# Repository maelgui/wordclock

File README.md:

# Wordclock

## Building the clock

This repository contains every files needed to build the clock

- PCB
- Vinyle cutout layout
- 3D model for diffuser

## Using the clock

Firmware for the clock and android app for managing it can be found here :

- https://github.com/maelgui/wordclock-firmware
- https://github.com/maelgui/wordclock-manager

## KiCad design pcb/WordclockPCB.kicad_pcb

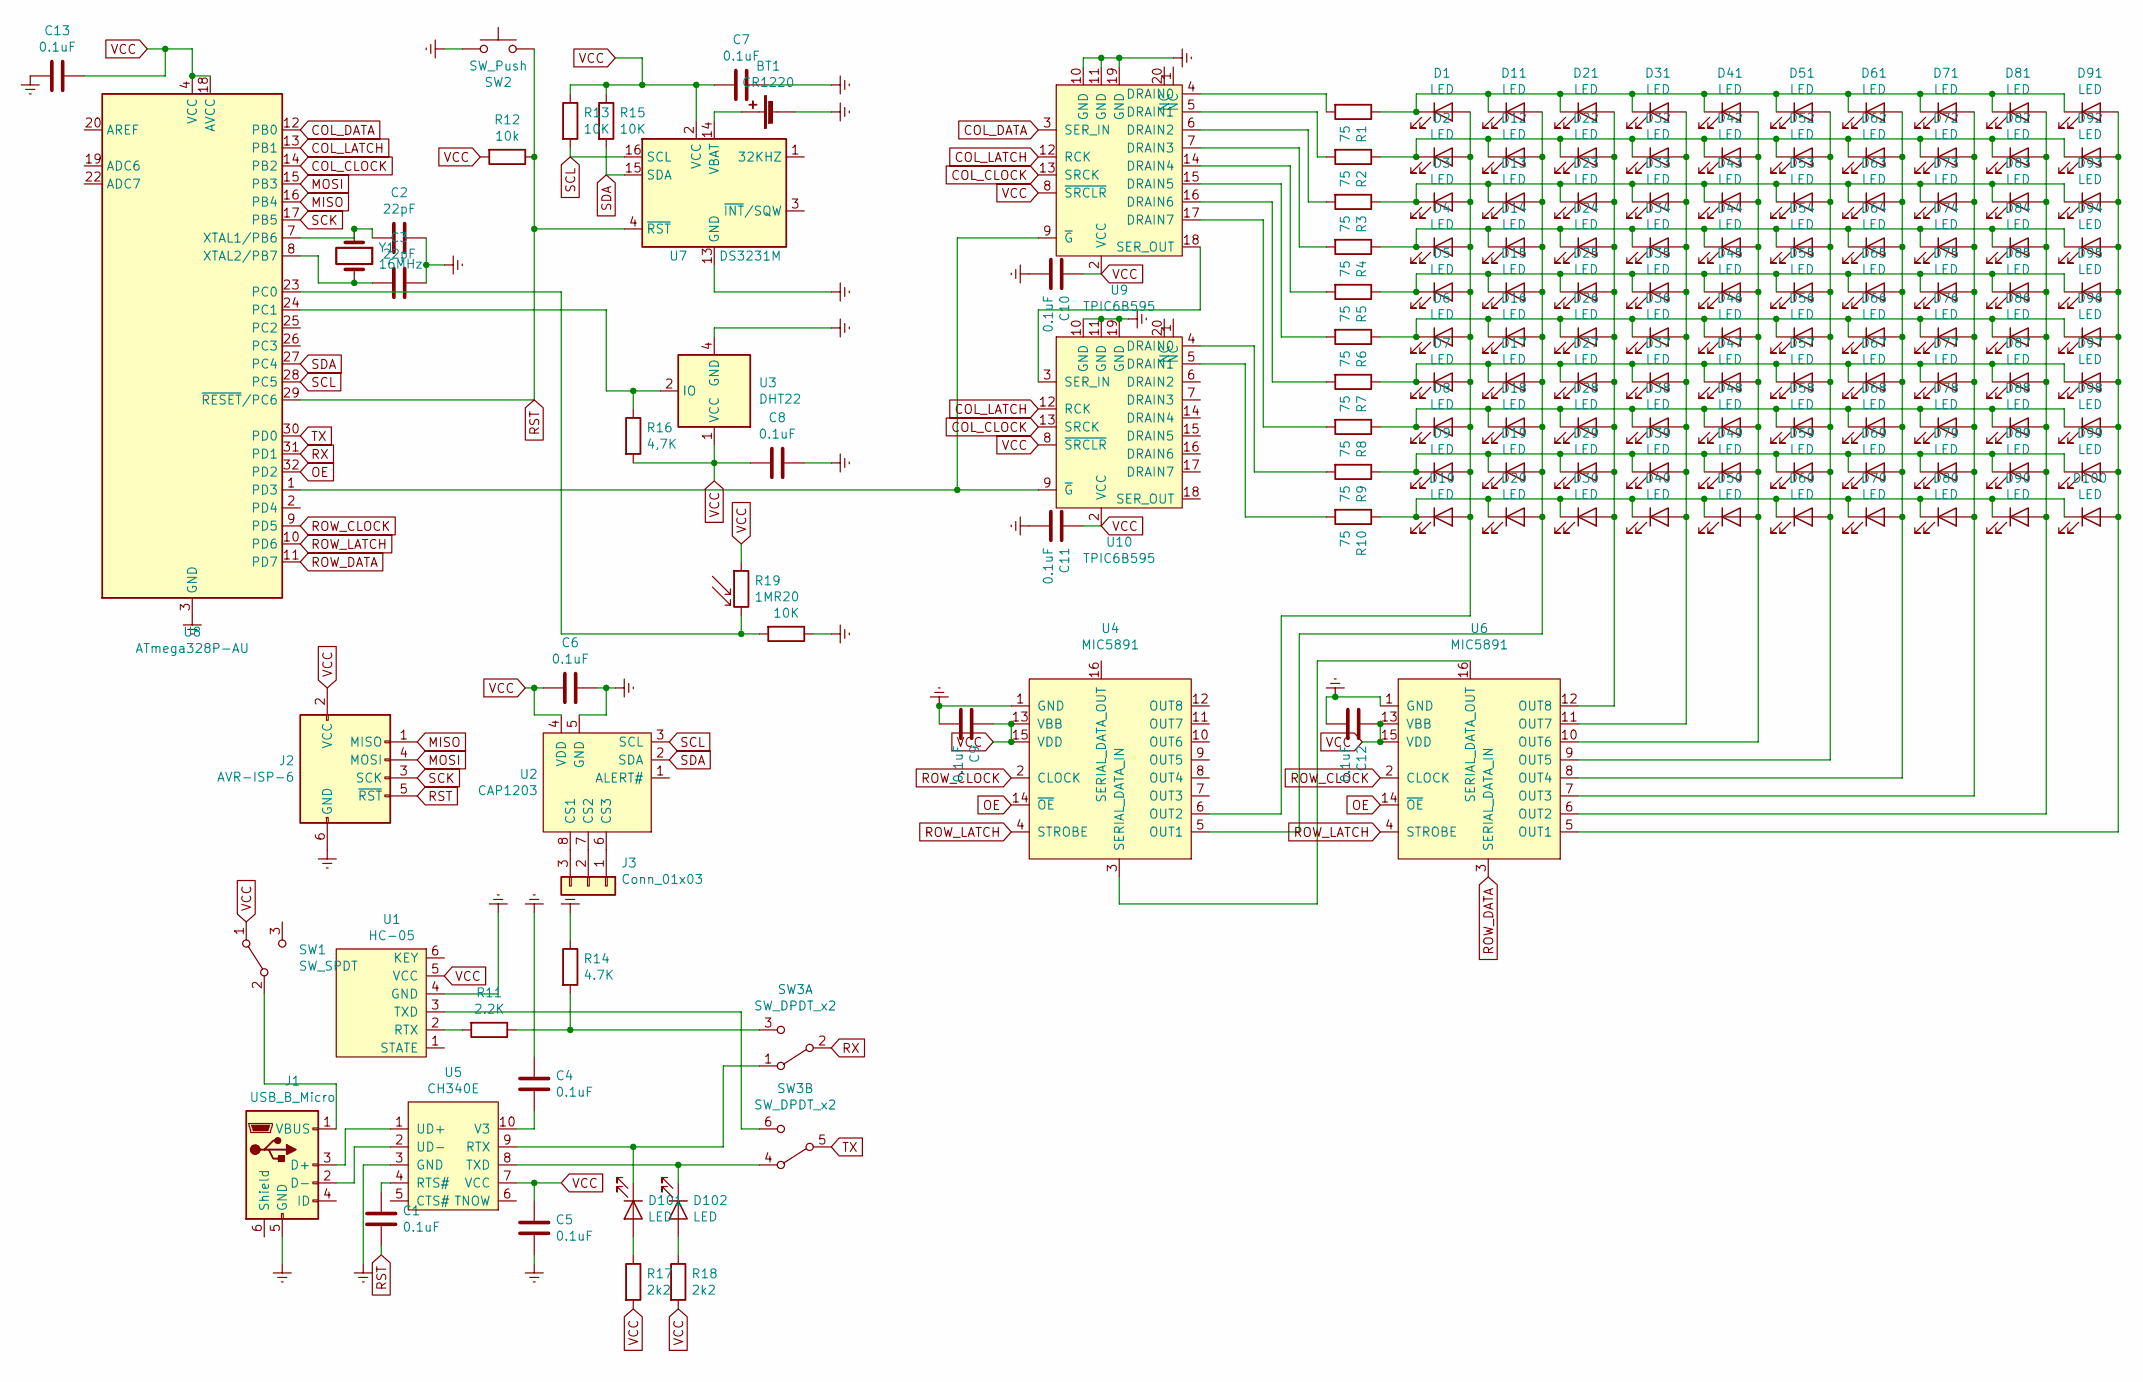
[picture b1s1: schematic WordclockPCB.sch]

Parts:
BT1: CR1220; BatteryHolder_MPD_BC2003_1x2032
C1, C4, C5, C6, C7, C8, C9, C10, C11, C12, C13: 0.1uF; C_0805_2012Metric
C2, C3: 22pF; C_0805_2012Metric
D1, D2, D3, D4, D5, D6, D7, D8, D9, D10, D11, D12, D13, D14, D15, D16, D17, D18, D19, D20, D21, D22, D23, D24, D25, D26, D27, D28, D29, D30, D31, D32, D33, D34, D35, D36, D37, D38, D39, D40, D41, D42, D43, D44, D45, D46, D47, D48, D49, D50, D51, D52, D53, D54, D55, D56, D57, D58, D59, D60, D61, D62, D63, D64, D65, D66, D67, D68, D69, D70, D71, D72, D73, D74, D75, D76, D77, D78, D79, D80, D81, D82, D83, D84, D85, D86, D87, D88, D89, D90, D91, D92, D93, D94, D95, D96, D97, D98, D99, D100: LED; LED_1210_3225Metric_Pad1.42x2.65mm_HandSolder
D101, D102: LED; LED_0805_2012Metric
J1: USB_B_Micro; USB_Micro-B_Amphenol_10103594-0001LF_Horizontal
J2: AVR-ISP-6; PinHeader_2x03_P2.54mm_Vertical_SMD
J3: Conn_01x03; PinHeader_1x03_P2.54mm_Vertical
R1, R2, R3, R4, R5, R6, R7, R8, R9, R10: 75; R_0805_2012Metric
R11: 2.2K; R_0805_2012Metric
R12: 10k; R_0805_2012Metric
R13, R15, R20: 10K; R_0805_2012Metric
R14: 4.7K; R_0805_2012Metric
R16: 4,7K; R_0805_2012Metric
R17, R18: 2k2; R_0805_2012Metric
R19: 1M; R_LDR_4.9x4.2mm_P2.54mm_Vertical
SW1: SW_SPDT; SW_SPDT_CK-JS102011SAQN
SW2: SW_Push; SW_Push_1P1T_NO_6x6mm_H9.5mm
SW3: SW_DPDT_x2; SW_JS202011SCQN
U1: HC-05; PinHeader_1x06_P2.54mm_Vertical
U2: CAP1203; SOIC-8_3.9x4.9mm_P1.27mm
U3: DHT22; Aosong_DHT11_5.5x12.0_P2.54mm
U4, U6: MIC5891; SOIC-16W_7.5x10.3mm_P1.27mm
U5: CH340E; TSSOP-10_3x3mm_P0.5mm
U7: DS3231M; SOIC-16W_7.5x10.3mm_P1.27mm
U8: ATmega328P-AU; TQFP-32_7x7mm_P0.8mm
U9, U10: TPIC6B595; SOIC-20W_7.5x12.8mm_P1.27mm
Y1: 16MHz; Crystal_SMD_HC49-SD_HandSoldering

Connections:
COL_CLOCK: U8.14 (PB2), U9.13 (SRCK), U10.13 (SRCK)
COL_DATA: U8.12 (PB0), U9.3 (SER_IN)
COL_LATCH: U8.13 (PB1), U9.12 (RCK), U10.12 (RCK)
Earth: BT1.2 (-), C2.1, C3.1, C4.2, C5.1, C6.1, C7.2, C8.2, C9.1, C10.1, C11.1, C12.1, C13.2, J1.5 (GND), J2.6 (GND), R14.1, R20.1, SW2.1, U1.4 (GND), U2.5 (GND), U3.4 (GND), U4.1 (GND), U5.3 (GND), U6.1 (GND), U7.5 (GND), U7.6 (GND), U7.7 (GND), U7.8 (GND), U7.9 (GND), U7.10 (GND), U7.11 (GND), U7.12 (GND), U7.13 (GND), U8.3 (GND), U8.5 (GND), U8.21 (GND), U9.10 (GND), U9.11 (GND), U9.19 (GND), U10.10 (GND), U10.11 (GND), U10.19 (GND); also elsewhere on the board
MISO: J2.1 (MISO), U8.16 (PB4)
MOSI: J2.4 (MOSI), U8.15 (PB3)
unnamed: BT1.1 (+), U7.14 (VBAT)
unnamed: C1.1, U5.4 (RTS#)
unnamed: C2.2, U8.7 (XTAL1/PB6), Y1.1
unnamed: C3.2, U8.8 (XTAL2/PB7), Y1.2
unnamed: C4.1, U5.10 (V3)
unnamed: D1.1 (K), D11.1 (K), D21.1 (K), D31.1 (K), D41.1 (K), D51.1 (K), D61.1 (K), D71.1 (K), D81.1 (K), D91.1 (K), R1.1
unnamed: D1.2 (A), D2.2 (A), D3.2 (A), D4.2 (A), D5.2 (A), D6.2 (A), D7.2 (A), D8.2 (A), D9.2 (A), D10.2 (A), U4.6 (OUT2)
unnamed: D10.1 (K), D20.1 (K), D30.1 (K), D40.1 (K), D50.1 (K), D60.1 (K), D70.1 (K), D80.1 (K), D90.1 (K), D100.1 (K), R10.1
unnamed: D11.2 (A), D12.2 (A), D13.2 (A), D14.2 (A), D15.2 (A), D16.2 (A), D17.2 (A), D18.2 (A), D19.2 (A), D20.2 (A), U4.5 (OUT1)
unnamed: D2.1 (K), D12.1 (K), D22.1 (K), D32.1 (K), D42.1 (K), D52.1 (K), D62.1 (K), D72.1 (K), D82.1 (K), D92.1 (K), R2.1
unnamed: D3.1 (K), D13.1 (K), D23.1 (K), D33.1 (K), D43.1 (K), D53.1 (K), D63.1 (K), D73.1 (K), D83.1 (K), D93.1 (K), R3.1
unnamed: D4.1 (K), D14.1 (K), D24.1 (K), D34.1 (K), D44.1 (K), D54.1 (K), D64.1 (K), D74.1 (K), D84.1 (K), D94.1 (K), R4.1
unnamed: D5.1 (K), D15.1 (K), D25.1 (K), D35.1 (K), D45.1 (K), D55.1 (K), D65.1 (K), D75.1 (K), D85.1 (K), D95.1 (K), R5.1
unnamed: D6.1 (K), D16.1 (K), D26.1 (K), D36.1 (K), D46.1 (K), D56.1 (K), D66.1 (K), D76.1 (K), D86.1 (K), D96.1 (K), R6.1
unnamed: D7.1 (K), D17.1 (K), D27.1 (K), D37.1 (K), D47.1 (K), D57.1 (K), D67.1 (K), D77.1 (K), D87.1 (K), D97.1 (K), R7.1
unnamed: D8.1 (K), D18.1 (K), D28.1 (K), D38.1 (K), D48.1 (K), D58.1 (K), D68.1 (K), D78.1 (K), D88.1 (K), D98.1 (K), R8.1
unnamed: D9.1 (K), D19.1 (K), D29.1 (K), D39.1 (K), D49.1 (K), D59.1 (K), D69.1 (K), D79.1 (K), D89.1 (K), D99.1 (K), R9.1
unnamed: D21.2 (A), D22.2 (A), D23.2 (A), D24.2 (A), D25.2 (A), D26.2 (A), D27.2 (A), D28.2 (A), D29.2 (A), D30.2 (A), U6.12 (OUT8)
unnamed: D31.2 (A), D32.2 (A), D33.2 (A), D34.2 (A), D35.2 (A), D36.2 (A), D37.2 (A), D38.2 (A), D39.2 (A), D40.2 (A), U6.11 (OUT7)
unnamed: D41.2 (A), D42.2 (A), D43.2 (A), D44.2 (A), D45.2 (A), D46.2 (A), D47.2 (A), D48.2 (A), D49.2 (A), D50.2 (A), U6.10 (OUT6)
unnamed: D51.2 (A), D52.2 (A), D53.2 (A), D54.2 (A), D55.2 (A), D56.2 (A), D57.2 (A), D58.2 (A), D59.2 (A), D60.2 (A), U6.9 (OUT5)
unnamed: D61.2 (A), D62.2 (A), D63.2 (A), D64.2 (A), D65.2 (A), D66.2 (A), D67.2 (A), D68.2 (A), D69.2 (A), D70.2 (A), U6.8 (OUT4)
unnamed: D71.2 (A), D72.2 (A), D73.2 (A), D74.2 (A), D75.2 (A), D76.2 (A), D77.2 (A), D78.2 (A), D79.2 (A), D80.2 (A), U6.7 (OUT3)
unnamed: D81.2 (A), D82.2 (A), D83.2 (A), D84.2 (A), D85.2 (A), D86.2 (A), D87.2 (A), D88.2 (A), D89.2 (A), D90.2 (A), U6.6 (OUT2)
unnamed: D91.2 (A), D92.2 (A), D93.2 (A), D94.2 (A), D95.2 (A), D96.2 (A), D97.2 (A), D98.2 (A), D99.2 (A), D100.2 (A), U6.5 (OUT1)
unnamed: D101.1 (K), SW3.1 (A), U5.9 (RTX)
unnamed: D101.2 (A), R17.1
unnamed: D102.1 (K), SW3.4 (A), U5.8 (TXD)
unnamed: D102.2 (A), R18.1
unnamed 35: J1.1 (VBUS), SW1.2 (B); also elsewhere on the board
unnamed 36: J1.2 (D-), U5.2 (UD-); also elsewhere on the board
unnamed 37: J1.3 (D+), U5.1 (UD+); also elsewhere on the board
unnamed 39: J1.6 (Shield); also elsewhere on the board
unnamed: J3.1, U2.6 (CS3)
unnamed: J3.2, U2.7 (CS2)
unnamed: J3.3, U2.8 (CS1)
unnamed: R1.2, U9.4 (DRAIN0)
unnamed: R2.2, U9.5 (DRAIN1)
unnamed: R3.2, U9.6 (DRAIN2)
unnamed: R4.2, U9.7 (DRAIN3)
unnamed: R5.2, U9.14 (DRAIN4)
unnamed: R6.2, U9.15 (DRAIN5)
unnamed: R7.2, U9.16 (DRAIN6)
unnamed: R8.2, U9.17 (DRAIN7)
unnamed: R9.2, U10.4 (DRAIN0)
unnamed: R10.2, U10.5 (DRAIN1)
unnamed: R11.1, R14.2, SW3.3 (C)
unnamed: R11.2, U1.2 (RTX)
unnamed: R16.1, U3.2 (IO), U8.24 (PC1)
unnamed: R19.2, R20.2, U8.23 (PC0)
unnamed: SW3.6 (C), U1.3 (TXD)
unnamed: U4.3 (SERIAL_DATA_IN), U6.16 (SERIAL_DATA_OUT)
unnamed: U9.18 (SER_OUT), U10.3 (SER_IN)
unnamed: U8.1 (PD3), U9.9 (~G), U10.9 (~G)
OE: U4.14 (~OE), U6.14 (~OE), U8.32 (PD2)
ROW_CLOCK: U4.2 (CLOCK), U6.2 (CLOCK), U8.9 (PD5)
ROW_DATA: U6.3 (SERIAL_DATA_IN), U8.11 (PD7)
ROW_LATCH: U4.4 (STROBE), U6.4 (STROBE), U8.10 (PD6)
RST: C1.2, J2.5 (~RST), R12.1, SW2.2, U7.4 (~RST), U8.29 (~RESET~/PC6)
RX: SW3.2 (B), U8.31 (PD1)
SCK: J2.3 (SCK), U8.17 (PB5)
SCL: R13.2, U2.3 (SCL), U7.16 (SCL), U8.28 (PC5)
SDA: R15.2, U2.2 (SDA), U7.15 (SDA), U8.27 (PC4)
TX: SW3.5 (B), U8.30 (PD0)
VCC: C5.2, C6.2, C7.1, C8.1, C9.2, C10.2, C11.2, C12.2, C13.1, J2.2 (VCC), R12.2, R13.1, R15.1, R16.2, R17.2, R18.2, R19.1, SW1.1 (A), U1.5 (VCC), U2.4 (VDD), U3.1 (VCC), U4.13 (VBB), U4.15 (VDD), U5.7 (VCC), U6.13 (VBB), U6.15 (VDD), U7.2 (VCC), U8.4 (VCC), U8.6 (VCC), U8.18 (AVCC), U9.2 (VCC), U9.8 (~SRCLR), U10.2 (VCC), U10.8 (~SRCLR)

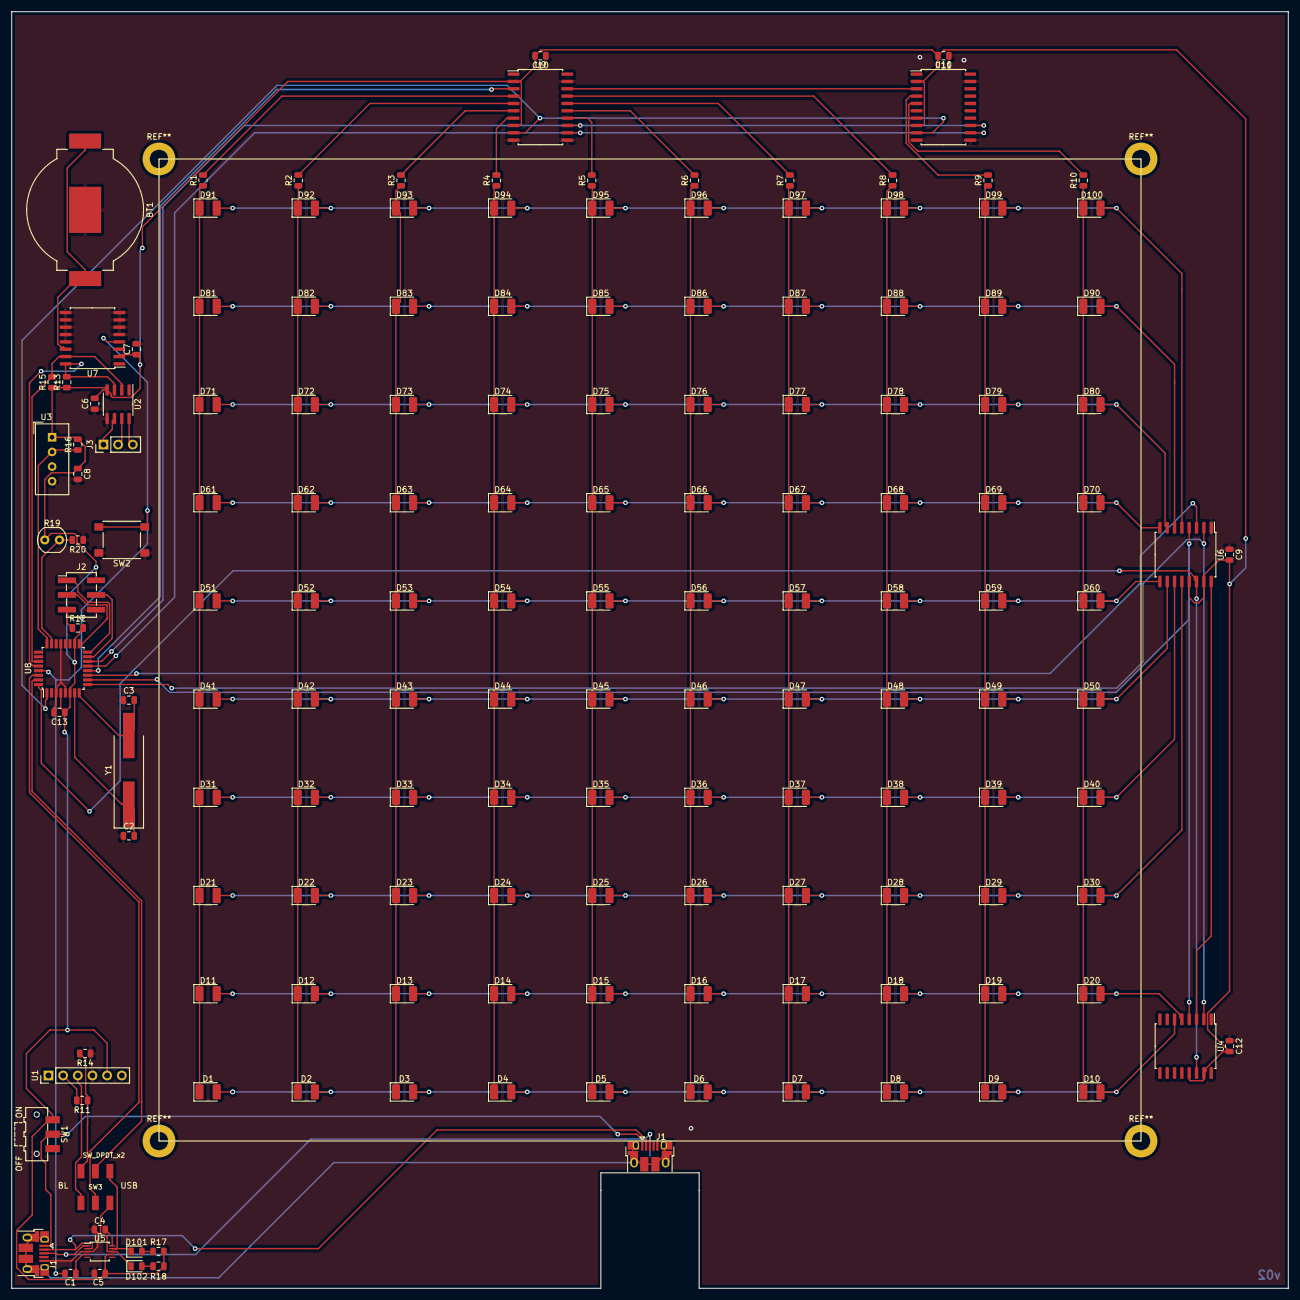
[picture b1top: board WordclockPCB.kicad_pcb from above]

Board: 2 copper layers, 221.0 x 221.0 mm, 154 parts (0 on the bottom side), 71 nets.

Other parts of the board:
J1#2: USB_B_Micro; USB_Micro-B_Amphenol_10103594-0001LF_Horizontal

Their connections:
Earth: J1#2.5; also elsewhere on the board
unnamed 35: J1#2.1; also elsewhere on the board
unnamed 36: J1#2.2; also elsewhere on the board
unnamed 37: J1#2.3; also elsewhere on the board
unnamed 39: J1#2.6; also elsewhere on the board

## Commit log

2021-07-20 First upload
2021-07-20 Add Readme
